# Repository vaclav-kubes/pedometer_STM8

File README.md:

# This repository serves as storage for my secondary school final thesis.
The aim of this thesis was design and implementation of pedometer with STM8 microcontroller and LCD display.
Detailed description is in this [PDF](/PDF/Dokumentace_DMP.pdf) (in czech).

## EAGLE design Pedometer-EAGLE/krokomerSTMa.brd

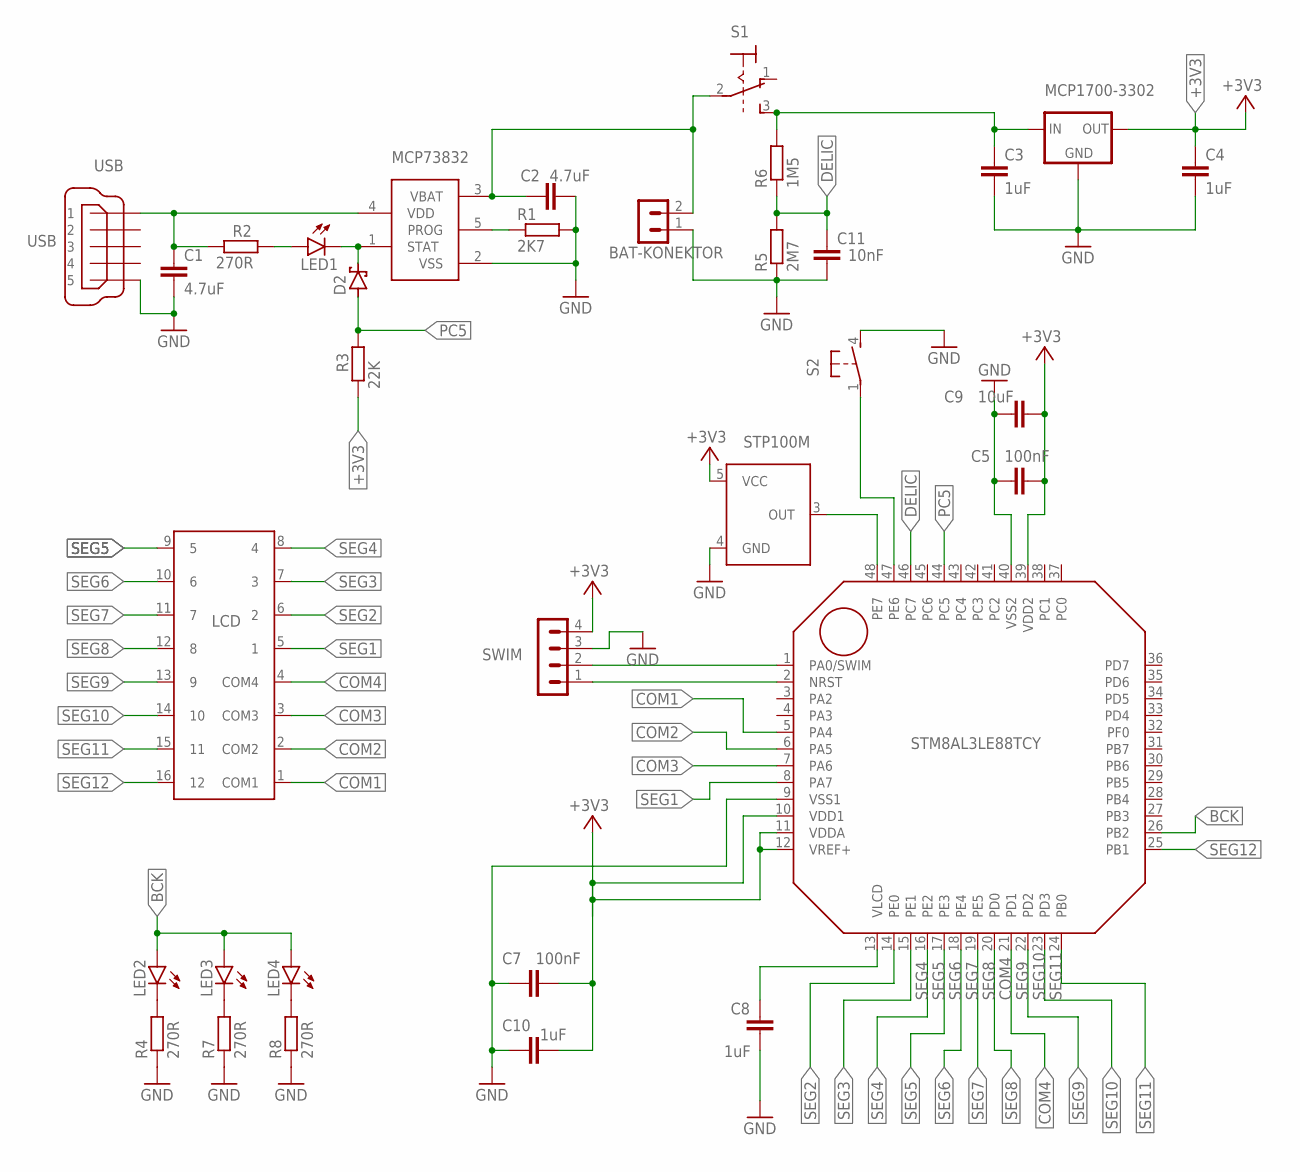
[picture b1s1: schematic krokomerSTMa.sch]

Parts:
BAT-KONEKTOR: PSH02-02P
C1, C2: 4.7uF; C0603
C3, C4, C8, C10: 1uF; C0603
C5, C7: 100nF; C0603
C9: 10uF; C0805
C11: 10nF; C0603
D2: BAT60J; SOD323_ST
LED1, LED2, LED3, LED4: LEDCHIPLED_0805; CHIPLED_0805
MCP1700: MCP1700-3302; SOT23
MCP73832: MCP73831; SOT23-5L
R1: 2K7; R0805
R2, R4, R7, R8: 270R; R0805
R3: 22K; R0805
R5: 2M7; R0805
R6: 1M5; R0805
S1: PREPINAC
S2: TLACITKO; DTSM-6
STM8AL3LE88: STM8AL3LE; TQFP48
SWIM: S1G4_JUMP; S1G4_JUM
U$1: LCD16
U$2: STP100M
USB: USB; 32005-301

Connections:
+3V3: C4.1, C5.1, C7.1, C9.2, C10.1, MCP1700.2 (OUT), R3.1, STM8AL3LE88.10 (VDD1), STM8AL3LE88.11 (VDDA), STM8AL3LE88.12 (VREF+), STM8AL3LE88.39 (VDD2), SWIM.4, U$2.5 (VCC)
BCK: LED2.A, LED3.A, LED4.A, STM8AL3LE88.26 (PB2)
COM1: STM8AL3LE88.5 (PA4), U$1.1 (COM1)
COM2: STM8AL3LE88.6 (PA5), U$1.2 (COM2)
COM3: STM8AL3LE88.7 (PA6), U$1.3 (COM3)
COM4: STM8AL3LE88.21 (PD1), U$1.4 (COM4)
DELIC: C11.1, R5.2, R6.1, STM8AL3LE88.46 (PC7)
GND: BAT-KONEKTOR.1, C1.2, C2.2, C3.2, C4.2, C5.2, C7.2, C8.2, C9.1, C10.2, C11.2, MCP1700.1 (GND), MCP73832.2 (VSS), R1.2, R4.1, R5.1, R7.1, R8.1, S2.4 (2), STM8AL3LE88.9 (VSS1), STM8AL3LE88.40 (VSS2), SWIM.3, U$2.4 (GND), USB.5; also elsewhere on the board
unnamed 8: MCP73832.5 (PROG), R1.1; also elsewhere on the board
unnamed: LED1.A, R2.2
unnamed 10: D2.C, LED1.C, MCP73832.1 (STAT); also elsewhere on the board
unnamed: C8.1, STM8AL3LE88.13 (VLCD)
unnamed: STM8AL3LE88.2 (NRST), SWIM.1
unnamed: STM8AL3LE88.1 (PA0/SWIM), SWIM.2
unnamed: S2.1, STM8AL3LE88.47 (PE6)
unnamed: LED2.C, R4.2
unnamed: STM8AL3LE88.48 (PE7), U$2.3 (OUT)
unnamed: LED3.C, R7.2
unnamed: C3.1, MCP1700.3 (IN), R6.2, S1.3 (S)
unnamed: LED4.C, R8.2
unnamed 20: C1.1, MCP73832.4 (VDD), R2.1, USB.1; also elsewhere on the board
PC5: D2.A, R3.2, STM8AL3LE88.44 (PC5); also elsewhere on the board
SEG1: STM8AL3LE88.8 (PA7), U$1.5 (1)
SEG2: STM8AL3LE88.14 (PE0), U$1.6 (2)
SEG3: STM8AL3LE88.15 (PE1), U$1.7 (3)
SEG4: STM8AL3LE88.16 (PE2), U$1.8 (4)
SEG5: STM8AL3LE88.17 (PE3), U$1.9 (5)
SEG6: STM8AL3LE88.18 (PE4), U$1.10 (6)
SEG7: STM8AL3LE88.19 (PE5), U$1.11 (7)
SEG8: STM8AL3LE88.20 (PD0), U$1.12 (8)
SEG9: STM8AL3LE88.22 (PD2), U$1.13 (9)
SEG10: STM8AL3LE88.23 (PD3), U$1.14 (10)
SEG11: STM8AL3LE88.24 (PB0), U$1.15 (11)
SEG12: STM8AL3LE88.25 (PB1), U$1.16 (12)
VCC: BAT-KONEKTOR.2, C2.1, MCP73832.3 (VBAT), S1.2; also elsewhere on the board

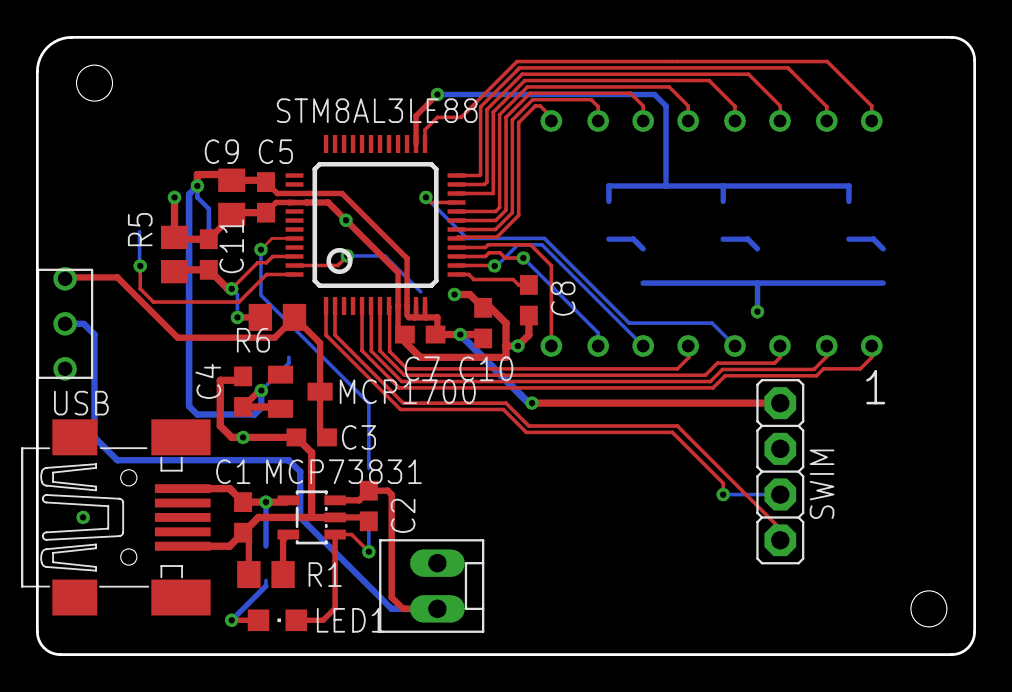
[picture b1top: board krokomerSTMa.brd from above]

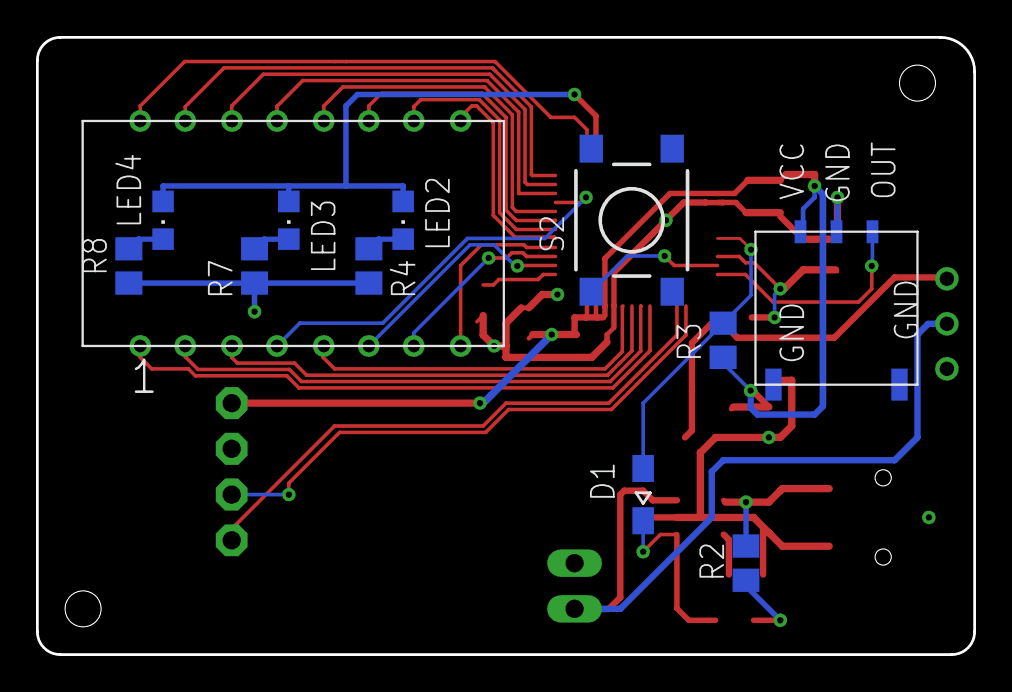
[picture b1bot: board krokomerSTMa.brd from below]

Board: 2 copper layers, 52.1 x 34.3 mm, 33 parts (12 on the bottom side), 35 nets.

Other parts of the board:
D1: SOD323-W
MCP73831: MCP73831; SOT23-5L

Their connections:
GND: MCP73831.2; also elsewhere on the board
unnamed 8: MCP73831.5; also elsewhere on the board
unnamed 10: D1.C, MCP73831.1; also elsewhere on the board
unnamed 20: MCP73831.4; also elsewhere on the board
PC5: D1.A; also elsewhere on the board
VCC: MCP73831.3; also elsewhere on the board

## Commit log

2024-02-28 files added
2024-02-28 pdf changed

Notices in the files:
parts and their libraries:
PaJa_konektory: Copyright (C) PaJa 2011
